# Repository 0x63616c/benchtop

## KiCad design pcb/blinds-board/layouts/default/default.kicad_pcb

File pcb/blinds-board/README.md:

# blinds driver rev C — 2S USB-PD charger + 12 V motor rail

One board per automated blind ([wayfinder #12](https://github.com/0x63616c/benchtop/issues/12),
layout [#22](https://github.com/0x63616c/benchtop/issues/22)). It charges a 2S3P
21700 pack from USB-C Power Delivery, boosts the pack to a 12 V rail **only
while the blind is moving**, and runs an ESP32-C3 on 3.3 V the rest of the time.

**88 × 32 mm, 6-layer, 1.6 mm FR4**, plus a snap-off 18 × 12 mm hall-sensor tab
below the board (panel is 88 × 47 mm). Rev C lies FLAT on the enclosure floor
(v2 center-drop unit): buttons + USB-C mouth out of the FRONT edge, 3× M3
mount holes onto printed bosses, and a plain enclosure pillar under the USB
edge (no 4th screw — that corner is the module antenna). Components on the
top side only; the two tactile switches (right-angle in rev C) and the three
XH connectors are through-hole.

## Power chain

```
USB-C ──► HUSB238A ──► BQ25798 ──┬──► BAT  2S3P 21700  (BQ29209 OV watchdog)
          PD sink,    buck-boost │
          12 V/3 A    charger    └──► SYS ─┬─► TPS61088 ──► 12 V ──► DRV8871 ──► motor
          by strap                         │   boost, EN-gated by the MCU
                                           └─► TLV62569 ──► 3V3 ──► ESP32-C3
```

SYS is alive from whichever source is present, so the MCU runs on the wall with
a flat pack, or on the pack with the wall unplugged. The 12 V rail is the only
thing that costs real quiescent current, and it is off unless a GPIO says
otherwise.

## Pinout

| ESP32-C3 | Signal | Goes to |
|---|---|---|
| IO4 / IO5 | IN1 / IN2 | DRV8871 — 00 coast, 10 fwd, 01 rev, 11 brake |
| IO6 | BOOST_EN | TPS61088 EN, with a 100 k pulldown |
| IO3 | HALL | DRV5032 push-pull output, via J4 |
| IO0 / IO1 | BTN_UP / BTN_DOWN | SW2 / SW1, to ground; use internal pull-ups |
| IO7 / IO8 | SCL / SDA | BQ25798, 4.7 k pull-ups to 3V3 |
| IO10 | /INT | BQ25798 interrupt, 10 k pull-up |
| IO18 / IO19 | USB D− / D+ | the USB-C receptacle — native USB, no bridge |
| IO2 | — | strapping pin, 10 k to 3V3, otherwise unused |

IO9 keeps its internal pull-up and there is **no BOOT button**: the C3's ROM
USB-Serial-JTAG enters download mode over the same USB-C that charges it.

> **The boost is off at reset and stays off until firmware says so.** That is
> the 100 k pulldown on IO6 doing its job — do not remove it to "fix" a board
> that does not move.

### Connectors

| Ref | Type | Pinout |
|---|---|---|
| J1 | USB-C 16-pin receptacle | PD input + native USB to the MCU |
| J2 | JST-XH 3-pin | Battery: `PACK+ / MID / PACK−`. The midpoint is what the BQ29209 balances on |
| J5 | JST-XH 2-pin | Motor: OUT1 / OUT2. Swap direction in firmware, not in the loom |
| J4 | JST-XH 3-pin | Hall: `3V3 / GND / DO` — cable to the tab |
| J3 | JST-XH 3-pin | On the **tab**: the other end of that cable |

> **In the enclosure the XH housings do not fit.** The slab between the wall
> and the motor tail is 4.4 mm and an XH shell is 5.75 mm tall. Solder the loom
> straight into the XH pads for a unit build; fit real housings only on the
> bench.

## The hall tab

The chain sprocket the hall sensor watches is ~80 mm from where the board
lives, so the DRV5032 cannot be on the board proper. It sits on a tab of the
same panel, joined by a 4 mm neck, with its own XH-3 facing J4. **Its three
nets are separate nets** (`p3v3_tab`, `gnd_tab`, `hall_do_tab`), so no copper
crosses the neck and snapping it off tears nothing.

## Configuration that is set by resistors, not firmware

| Part | Strap | Value | Why |
|---|---|---|---|
| HUSB238A | SNK_VSET | 6.04 k 1 % | request 12 V (datasheet window 5.7–6.3 k) |
| HUSB238A | SNK_ISET | 21 k 1 % | request 3 A (window 19.95–22.05 k) |
| BQ25798 | PROG | 8.2 k 1 % | 2 cells at 750 kHz — which is what makes 2.2 µH the right inductor |
| BQ25798 | ILIM_HIZ | tied to REGN | maximum input limit; the real one is an I²C register |
| BQ25798 | TS | 10 k / 10 k off REGN | no pack NTC in rev B: hold TS mid-window so charging is never suspended |
| TPS61088 | FSW → SW | 200 k | ≈770 kHz at 8 V in / 12 V out |
| TPS61088 | ILIM | 200 k | 5.95 A typical switch limit (1190000/R, PFM) |
| TPS61088 | FB | 200 k / 22 k | 12.15 V from a 1.204 V reference |
| TLV62569 | FB | 100 k / 22 k | 3.33 V from a 0.6 V reference |
| DRV8871 | ILIM | 30 k | 2.1 A trip — the datasheet's own worked example |

**Cell count is not a strap.** PROG only sets the power-up default; firmware
must configure 2S over I²C before enabling charge.

## Build loop

```
ato build                       # twice after adding a component — nets stamp a build late
PCB_BOARD=blinds-board just pcb place   # placement + routing + preview.svg
PCB_BOARD=blinds-board just pcb drc     # + real KiCad DRC
PCB_BOARD=blinds-board just pcb build   # + renders + gerbers/BOM/CPL
PCB_BOARD=blinds-board just pcb view    # live 3D board in this pane
```

Placement and routing are data tables in `tools/place_and_render.py`;
`tools/router.py` is the A* grid router that turns them into copper. Neither
one is a black box — read their docstrings before moving a part.

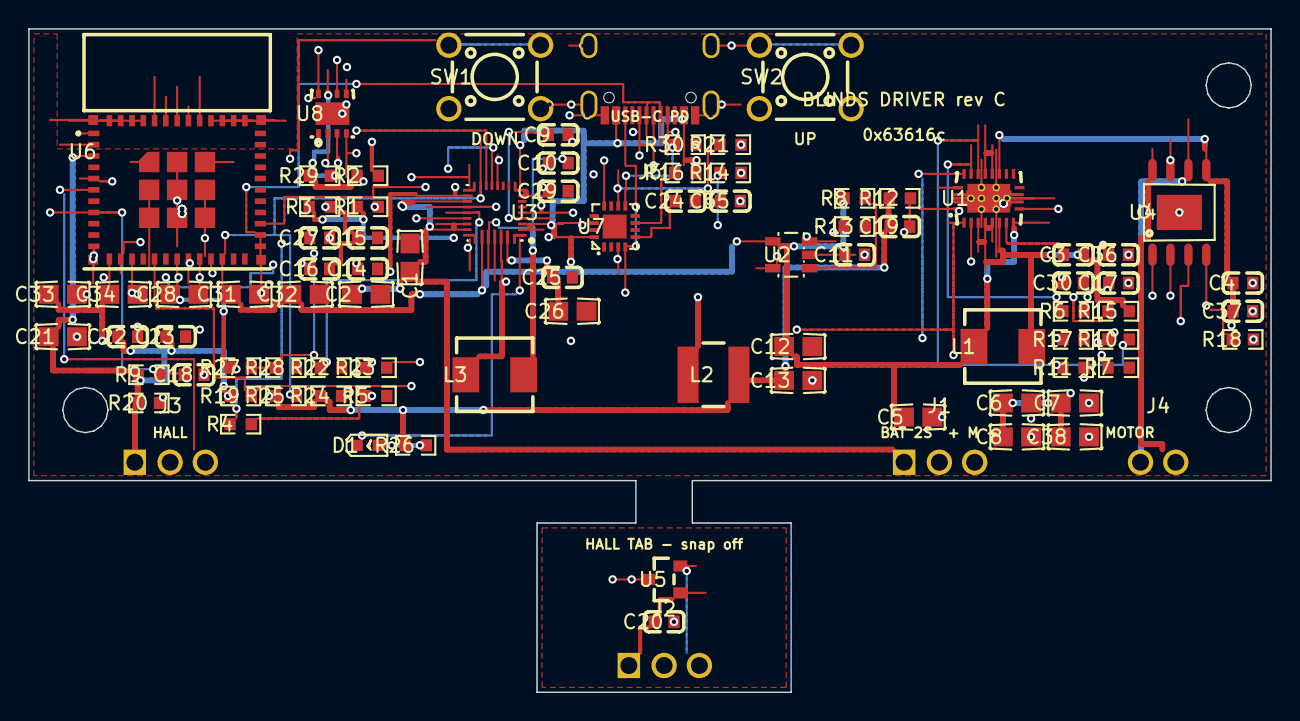
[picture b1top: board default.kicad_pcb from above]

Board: 6 copper layers, 88.0 x 47.0 mm, 87 parts (0 on the bottom side), 64 nets.

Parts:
C1, C2, C5, C6, C7, C8, C12, C13, C21, C26, C28, C31, C32, C33, C34, C38: C0805
C3, C4, C9, C10, C11, C14, C15, C16, C17, C18, C19, C20, C22, C23, C24, C25, C27, C29, C30, C35, C36, C37: C0603
D1: LED0603-RD
J1, J2, J3: CONN-TH_3P-P2.50_XH-3A
J4: CONN-TH_2P-P2.50_XH-2AW
J5: USB-C_SMD-TYPE-C-31-M-12_1
L1, L3: IND-SMD_L5.4-W5.2_FXL0530
L2: IND-SMD_L4.0-W4.0_LQH44PN2R2MP0L
R1, R2, R3, R4, R5, R6, R7, R8, R9, R10, R11, R12, R13, R14, R15, R16, R17, R18, R19, R20, R21, R22, R23, R24, R25, R26, R27, R28, R29, R30: R0603
SW1, SW2: SW-TH_4P-L6.0-W6.0-P4.50-LS6.5
U1: VQFN-20_L4.6-W3.6-P0.50-BL
U2: SOT-23-5_L3.0-W1.7-P0.95-LS2.8-BR
U3: QFN-29_L4.0-W4.0-P0.40-TL-BQ25792RQMR
U4: SO-8_L4.9-W3.9-P1.27-LS6.0-BL-EP
U5: SOT-23_L2.9-W1.3-P1.90-LS2.4-BR
U6: WIFIM-SMD_ESP32-C3-MINI-1
U7: QFN-16_L3.0-W3.0-P0.50-BL-EP1.7
U8: SON-8_L3.0-W3.0-P0.65-LS3.0-BL-EP

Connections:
1: C1.1, C2.1, J1.1, R2.1, R29.1, U3.18, U3.22, U3.23
1-1: C4.1, C6.1, C7.1, C8.1, C37.1, C38.1, R10.1, U1.14, U1.15, U1.16, U4.5
1-2: C5.1, C11.1, C12.1, C31.1, C32.1, L1.1, R8.1, U1.9, U2.4, U3.25
1-3: C13.1, C19.1, C21.1, C22.1, C23.1, J3.1, L2.2, R9.1, R12.1, R19.1, R20.1, R24.1, R25.1, R26.1, U6.3
1-4: C16.1, R2.2, U8.1
1-5: C20.1, J2.1, U5.1
1-6: C28.1, R23.1, R27.1, U3.5, U3.17
1-7: R16.1, U7.7
2: C1.2, C2.2, C4.2, C5.2, C6.2, C7.2, C8.2, C11.2, C12.2, C13.2, C14.2, C15.2, C17.2, C18.2, C21.2, C22.2, C23.2, C24.2, C25.2, C26.2, C27.2, C28.2, C29.2, C30.2, C31.2, C32.2, C33.2, C34.2, C35.2, C36.2, C37.2, C38.2, J1.3, J3.2, J5.1, J5.2, J5.3, J5.4, J5.A1B12, J5.B1A12, R5.2, R7.2, R11.2, R13.2, R14.2, R16.2, R17.2, R18.2, R21.2, R22.2, R28.2, R30.2, SW1.3, SW1.4, SW2.3, SW2.4, U1.20, U1.21, U2.2, U3.27, U4.1, U4.7, U4.9, U6.1, U6.2, U6.11, U6.14, U6.36, U6.37, U6.38, U6.39, U6.40, U6.41, U6.42, U6.43, U6.44, U6.45, U6.46, U6.47, U6.48, U6.49, U6.50, U6.51, U6.52, U6.53, U7.12, U7.17, U8.5, U8.6, U8.9
2-1: C3.2, L1.2, R15.2, U1.4, U1.5, U1.6, U1.7
2-2: C10.2, L3.2, U3.26
2-3: C15.1, C16.2, R3.2, U8.2
18: U4.3, U6.18
19: U4.2, U6.19
CC1: J5.A5, U7.3
CC2: J5.B5, U7.4
FLGIN: R14.1, U7.14
SNK_ISET: R21.1, U7.10
SNK_VSET: R30.1, U7.9
VBUS: C33.1, C34.1, C35.1, J5.A4B9, J5.B4A9, U3.2, U3.3, U3.8, U3.9, U7.16
VDD: C24.1, U7.5
batmid: J1.2, R1.1, R3.1
boot_bst: C3.1, U1.8
btn_dn: SW1.1, SW1.2, U6.13
btn_up: SW2.1, SW2.2, U6.12
btst1: C9.1, U3.4
btst2: C10.1, U3.19
chg_ce: R4.2, R5.1, U3.13
chg_int: R19.2, U3.21, U6.16
chg_qon: R23.2, U3.12
chg_stat: D1.1, U3.1
comp_bst: R6.1, U1.18
comp_mid: C17.1, R6.2
en_bst: R7.1, U1.2, U6.20
en_buck: R8.2, U2.1
fb_bst: R10.2, R11.1, U1.17
fb_buck: C19.2, R12.2, R13.1, U2.5
fsw_bst: R15.1, U1.3
gnd_tab: C20.2, J2.2, U5.3
hall_do: J3.3, U6.6
hall_do_tab: J2.3, U5.2
ilim_bst: R17.1, U1.19
ilim_mot: R18.1, U4.4
io2: R20.2, U6.5
mcu_en: C18.1, R9.2, U6.8
mot_a: J4.1, U4.6
mot_b: J4.2, U4.8
ov_out: R4.1, U8.8
pmid: C25.1, C26.1, U3.29
prog: R22.1, U3.20
prot_cb: R1.2, U8.3
prot_cd: C14.1, U8.4
prot_vdd: C27.1, R29.2, U8.7
scl: R24.2, U3.14, U6.21
sda: R25.2, U3.15, U6.22
sdrv: C29.1, U3.24
ss_bst: C30.1, U1.10
stat_a: D1.2, R26.2
sw_buck: L2.1, U2.3
sw_chg1: C9.2, L3.1, U3.28
ts: R27.2, R28.1, U3.16
usb_dn: J5.A7, J5.B7, U6.26
usb_dp: J5.A6, J5.B6, U6.27
vcc_bst: C36.1, U1.1
